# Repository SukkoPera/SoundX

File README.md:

# SoundX

SoundX is an Open Hardware sound card for the Commodore 16, 116 and Plus/4 home computers based on the Yamaha OPL/OPL-II chip.

## Summary
SoundX is basically an adaptation of the [C64 SFX Sound Expander](https://www.c64-wiki.com/wiki/Commodore_Sound_Expander) for the x264 series of Commodore computers.

While it didn't enjoy much success when it was released on the C64, since it was not that much superior to the built-in SID (if superior at all...), it would have certainly been much more successful if it had been targeted at the Commodore 16, 116 and Plus/4. In fact, it is basically the equivalent of an [AdLib](https://en.wikipedia.org/wiki/Ad_Lib,_Inc.#AdLib_Music_Synthesizer_Card_(1987)), an audio card for the PCs of the time, based on the YM3526 chip from Yamaha (also known as OPL), which is *exponentially* better than the TED as a sound chip, as it sports the following features (thanks [Wikipedia](https://en.wikipedia.org/wiki/Yamaha_OPL)):

- 9 channels of sound, each made of two oscillators or 6 channels with 5 percussion instruments

For every channel:
- Main frequency (10 bits)
- Octave (3 bits)
- Note on/off
- Synthesis mode (FM or just additive)
- Feedback (0–7, the modulator modulating itself)

For each one of the two oscillators:
- Frequency multiply (can be set to 1⁄2, 1 to 10, 12 or 15)
- Waveform (Sine)
- Volume (0–63, logarithmic)
- Attack, decay, sustain, release (4 bits each, logarithmic)
- Tremolo (on or off)
- Vibrato (on or off)
- Sustain (on or off)
- Envelope scaling per key (on or off)
- Volume scaling per key (0–3)

There are also a few parameters that can be set for the whole chip:
- Vibrato depth
- Tremolo depth
- Percussion mode (uses 3 channels to provide 5 percussion sounds)
- Composite sine mode (see Sinewave synthesis)

The board can even use the slightly more modern YM3812 (OPL-II): *among its newly-added features is the ability to pick between four waveforms for each individual oscillator. In addition to the original sine wave, three modified waveforms can be produced: half-sine waves (where the negative part of the sine is muted), absolute-sine waves (where the negative part is inverted), and pseudo-sawtooth waves (quarter sine waves upward only with silent sections in between)*.

### MIDI I/O
The original SFX Sound Expander could be bought [together with a piano-like keyboard](http://www.mssiah-forum.com/viewtopic.php?pid=4598#p4598) and some demo software. Such keyboard is not easy to find these days, so it was pointless to replicate the interface for it and I rather decided to build upon my experience with another project and add a real MIDI I/O interface. This means the C16/116/+4 will be able to receive data from a MIDI keyboard or to play it, through a **standard** DIN-5 MIDI interface.

## Versions
There are currently two versions of SoundX. Both have the same features and differ only in a few aspects, see below for more details.

## Design and Assembly Notes
This project makes sense because the YM3812 chip, its companion DAC (YM3014B) and an ACIA chip (for the MIDI part) can all be bought supercheap on AliExpress & similar sites, making this board very affordable to build for everyone. Let's say 15-20€? So get all this stuff second-hand and be happy :).

Remember to solder the JP5 jumper on the back of the board: I suggest the ON position unless you know what you are doing (check the schematics).

The audio output is automatically fed back into the computer through the EXT_AUDIO pin, so that you will hear it mixed with the sounds produced by the TED. There is also a 3.5" jack connector on the board, which allows bringing the sound output to external equipment. Note that when a jack is plugged in, the sound will no longer be redirected to the EXT_AUDIO pin.

Note that the OPL and MIDI circuits of the board are completely independent from each other, so the board can also be assembled partially if only one of the features is desired. The IBOM points out which feature every components belongs to.

### Version 1
Version 1 uses a standard ACIA 6551 chip for the MIDI interface. This is available from different manufacturers (MOS, Rockwell, and even [new from the Western Design Center](https://www.westerndesigncenter.com/wdc/w65c51s-chip.php)!) and requires a 3 MHz crystal to reach the MIDI baudrate.

The YM3812 requires an active oscillator either in DIP-8 or DIP-14 size.

There are some solder jumpers on the board:
- JP1: Close if your oscillator requires pin 1 to be grounded (uncommon).
- JP2: Close if you want the same signal sent to both channels of the jack connector.
- JP3/JP4: Close these to provide +5V on the normally-unused pins of the MIDI output connector: **this is non-standard and might actually damage the board or the connected device**, so keep these open unless you REALLY know what you are doing.
- JP5: The YM3812 can either go through a 15 kHz low-pass filter (ON) or not (BYPass): normally set to ON.

### Version 2
Version 2 switched the ACIA to a Motorola MC6850 chip that requires an active oscillator in DIP-8 size, running at either 500 kHz or 2 MHz. When using the 500 kHz oscillator, U5 and C12 are not required and can be skipped altogether.

In order to make space for the MC6850 oscillator, the YM3812 oscillator was also restricted to DIP-8 size.

Version 2 features additional jumpers:
- JP6: Same as JP1 for the MC6850 oscillator.
- JP7: Set in accordance with the oscillator frequency.
- JP8: Set to R/W and don't ask questions! If you want to know more, see [this](https://github.com/mist-devel/c64/issues/1).

## Programming
### OPL/OPL-II
Due to the impressive array of features, the OPL/OPL-II is not easy to program: the chip has 244 registers, so it would take a while to get acquainted with it and there is really not much documentation about how to program the SFX Sound Expander. This is one of the reasons why I decided to diverge a bit from the SFX Sound Expander on the programming side and rather followed the AdLib style: the board only uses two addresses for the audio part: $FDE4 and $FDE5. The former is for writing the number of the YM register to be modified while the latter is for the value. The former address can also be read and it will return the OPL status register, which is only useful for the detection of the board or if you want to make use of the OPL internal timers.

This means that you should be able to follow any AdLib programming tutorials around (like [this one](https://bochs.sourceforge.io/techspec/adlib_sb.txt)), as they should be 100% applicable to SoundX just as well (except for the different addresses, of course). The chip detection from that document also works!

> [!IMPORTANT]
> When programming the OPL chip, always keep in mind is that **you must wait at least 3.3 microseconds after you wrote the address, before you write the data, and then at least 23 microseconds before the next write**. This stands for AdLib sound cards as well, since it is an inherent limitation of the OPL chip. Nevertheless, [some clever programming](https://c64.xentax.com/index.php/15-testing-ym3812-register-write-timing) appears to be able to mitigate the issue.

### MIDI I/O - Version 1
The classic ACIA (6551) chip running the MIDI section uses addresses $FDE0/1/2/3 (I chose these addresses because they were already partly used by Solder's MIDI interface).

Configure the chip for:
- No Parity, No Echo, No TX Interrupt, /RTS Low (Unneeded), No RX Interrupt, /DTR Low (Unneeded) &rarr; $0b to Command Register
- 0 Stop Bits, 8 Data Bits, Internal Baud Rate Generator, 19200 bps (which will actually result in 31250 due to the use of the non-standard crystal) &rarr; $1f to Control Register

### MIDI I/O - Version 2
The MC6850 only has two register, which get mapped at $FDE0/1, which makes me think that this is exactly the same design used by Solder's interface. The software configuration is the same, regardless of what oscillator is installed: configure the chip for No interrupt, /RTS Low (Unneeded), 8 Data bits + 1 Stop bit, No Parity, Clock Divider = 16 (i.e.: $15)

> [!NOTE]
> Please always support both board versions in your projects. It is easy and you can find a driver that does so on the [Wiki](https://github.com/SukkoPera/SoundX/wiki).

### Examples
If you want some code to start from, you can have a look at the [Tech Demo that Master Csabo from the Plus/4 World Forum quickly hacked together](https://plus4world.powweb.com/software/YM3812_Tech_Demo): it does OPL detection and then plays a few songs from the original [AdLib Card Demo](https://vgmrips.net/packs/pack/adlib-music-synthesizer-card-demo-songs-ibm-pc-xt-at). It comes with full source code, so it will definitely be helpful!

Csabo has also made a [Simple MIDI Decoder](https://plus4world.powweb.com/software/Simple_MIDI_Decoder) utility that listens for NoteOn and NoteOff messages coming in through the MIDI port and plays the corresponding notes through the TED. Again, it comes with full source code and thus it should help you have a jump start.

## Next Steps
Of course, to make complete sense, this project needs support from the actual programmers! So people, please make games for the board! Or programs, demos, whatever! I think a nice first step would be to port [the original SFX Sounds Expander software](https://csdb.dk/release/?id=155181): I can't say for sure, but I'm guessing this shouldn't be too much of an effort, plus I can help with the tech details and can explain how to make the MIDI decoder, just ask! :)

## Releases
If you want to get this board produced, you are recommended to get [the latest release](https://github.com/SukkoPera/SoundX/releases) rather than the current git version, as the latter might be under development and is not guaranteed to be working.

Every release is accompanied by its Bill Of Materials (BOM) file and any relevant notes about it, which you are recommended to read carefully.

## License
The SoundX documentation, including the design itself, is copyright &copy; SukkoPera 2023-2025 and is licensed under the [Creative Commons Attribution-NonCommercial-ShareAlike 4.0 International License](https://creativecommons.org/licenses/by-nc-sa/4.0/).

This documentation is distributed *as is* and WITHOUT ANY EXPRESS OR IMPLIED WARRANTIES whatsoever with respect to its functionality, operability or use, including, without limitation, any implied warranties OF MERCHANTABILITY, SATISFACTORY QUALITY, FITNESS FOR A PARTICULAR PURPOSE or infringement. We expressly disclaim any liability whatsoever for any direct, indirect, consequential, incidental or special damages, including, without limitation, lost revenues, lost profits, losses resulting from business interruption or loss of data, regardless of the form of action or legal theory under which the liability may be asserted, even if advised of the possibility or likelihood of such damages.

## Support the Project
If you want to get some boards manufactured, you can get them from PCBWay through this link:

You get my gratitude and cheap, professionally-made and good quality PCBs, I get some credit that will help with this and [other projects](https://www.pcbway.com/project/member/?bmbno=72D33927-5EF6-42). You won't even have to worry about the various PCB options, it's all pre-configured for you!

Also, if you still have to register, [you can use this link](https://www.pcbway.com/setinvite.aspx?inviteid=41100) to get some bonus initial credit (and yield me some more).

You can also buy me a coffee if you want, all the money collected this way will actually go to charity:

## Thanks
* Master Csabo and Chizman (unbeknownst) for their help with the testing software.
* kinmami for his usual precious hints about the hardware design.
* Iconian Fonts (Daniel Zadorozny) for the [Universal Jack Font](https://www.fontspace.com/universal-jack-font-f101650) used for the logo.

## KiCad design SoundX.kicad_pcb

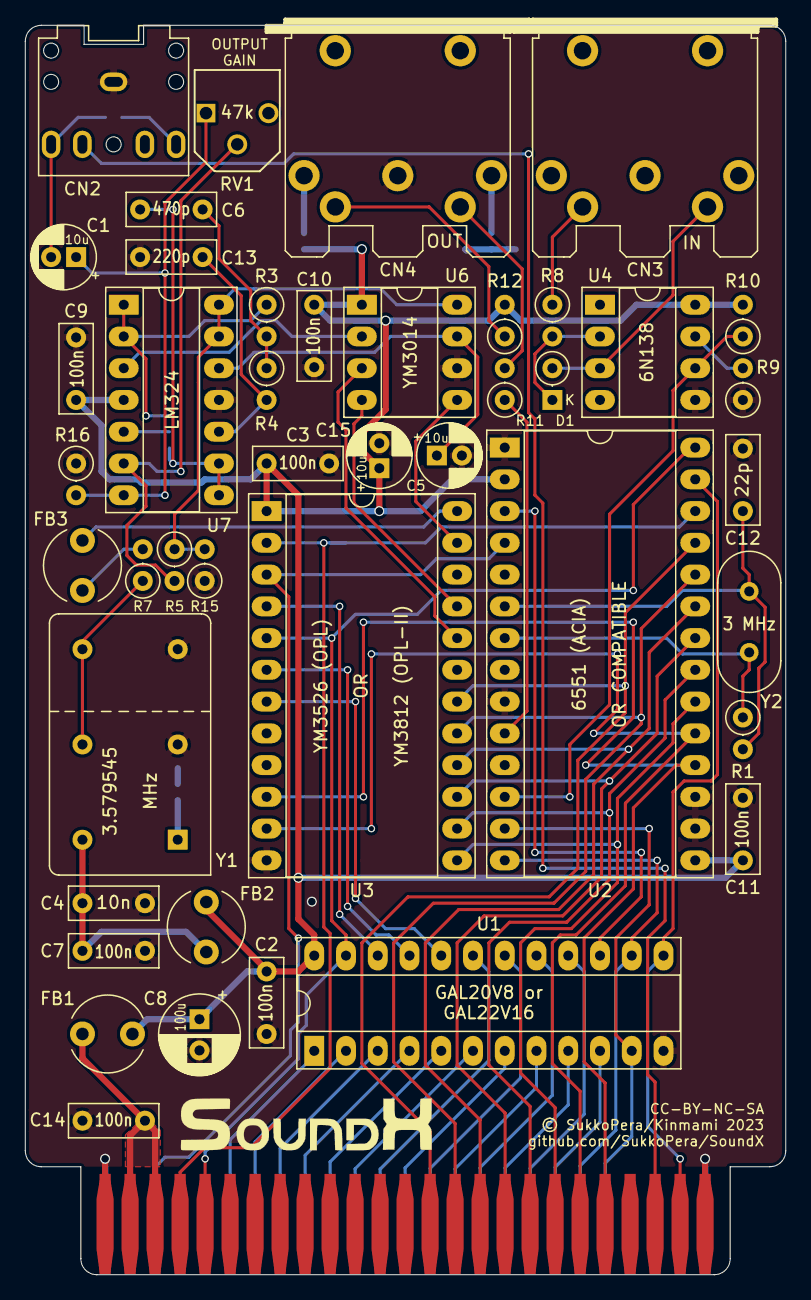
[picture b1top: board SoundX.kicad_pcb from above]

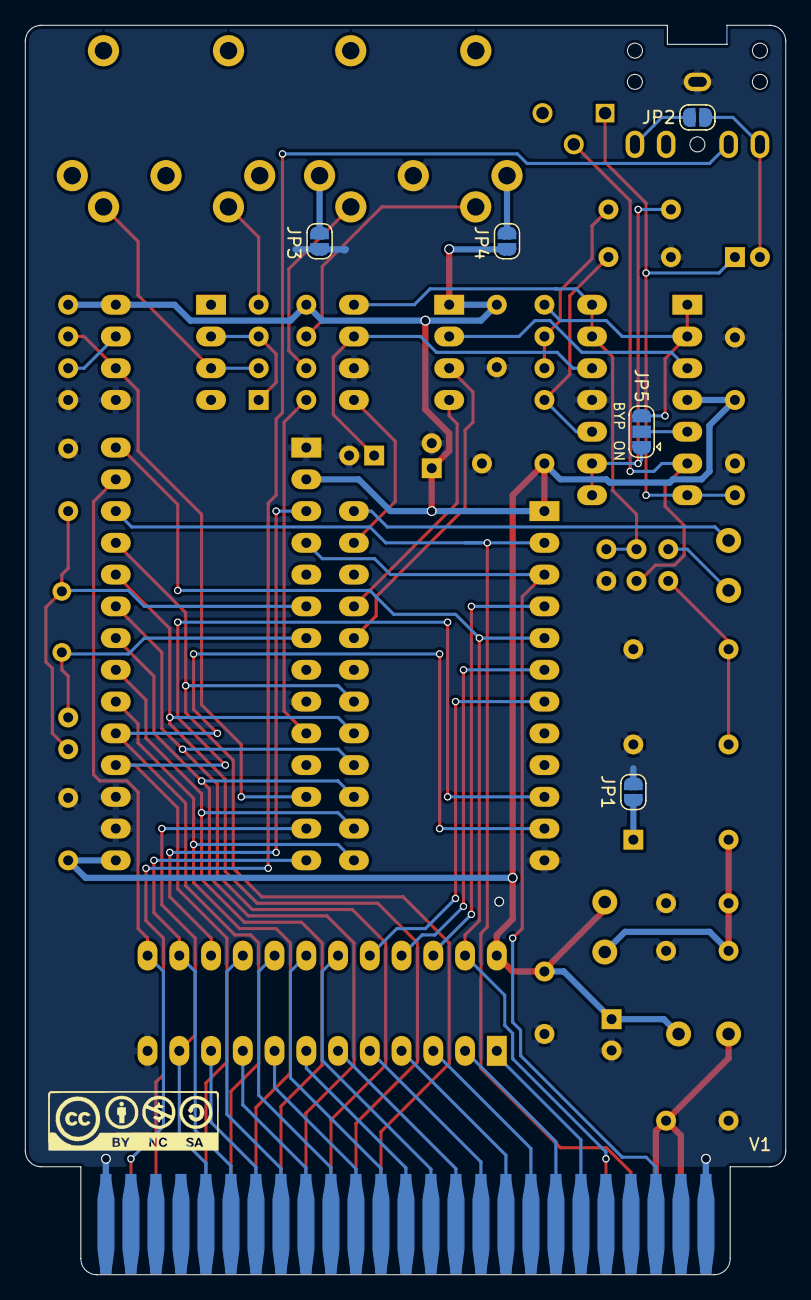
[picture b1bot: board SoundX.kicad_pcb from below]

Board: 2 copper layers, 60.8 x 99.9 mm, 51 parts (6 on the bottom side), 68 nets.

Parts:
C1, C5, C15: 10u; CP_Radial_D5.0mm_P2.00mm
C2, C3, C7, C9, C10, C11, C14: 100n; C_Disc_D7.0mm_W2.5mm_P5.00mm
C4: 10n; C_Disc_D7.0mm_W2.5mm_P5.00mm
C6: 470p; C_Disc_D7.0mm_W2.5mm_P5.00mm
C8: 100u; CP_Radial_D6.3mm_P2.50mm
C12: 22p; C_Disc_D7.0mm_W2.5mm_P5.00mm
C13: 220p; C_Disc_D7.0mm_W2.5mm_P5.00mm
CN1: EDGE_CONN; C16_Cart_Conn
CN2: RAW_AUDIO_OUT; AudioJack_SJ1-3525N
CN3: CONN_MIDI_IN; DIN5
CN4: CONN_MIDI_OUT; DIN5
D1: 1n4148; D_DO-35_SOD27_P2.54mm_Vertical_KathodeUp
FB1, FB2, FB3: FERRITE; L_Radial_D6.0mm_P4.00mm
JP1: JMP_OSC_PIN1; SolderJumper-2_P1.3mm_Open_RoundedPad1.0x1.5mm
JP2: JMP_STEREO; SolderJumper-2_P1.3mm_Open_RoundedPad1.0x1.5mm
JP3: JMP_POM_GND; SolderJumper-2_P1.3mm_Open_RoundedPad1.0x1.5mm
JP4: JMP_POM_VCC; SolderJumper-2_P1.3mm_Open_RoundedPad1.0x1.5mm
JP5: JMP_FILTER_BYPASS; SolderJumper-3_P1.3mm_Open_RoundedPad1.0x1.5mm
R1: 1M; R_Axial_DIN0207_L6.3mm_D2.5mm_P2.54mm_Vertical
R3, R4: 33k; R_Axial_DIN0207_L6.3mm_D2.5mm_P2.54mm_Vertical
R5: 15k; R_Axial_DIN0207_L6.3mm_D2.5mm_P2.54mm_Vertical
R7: 47; R_Axial_DIN0207_L6.3mm_D2.5mm_P2.54mm_Vertical
R8, R10, R11, R12: 220; R_Axial_DIN0207_L6.3mm_D2.5mm_P2.54mm_Vertical
R9, R15: 4.7k; R_Axial_DIN0207_L6.3mm_D2.5mm_P2.54mm_Vertical
R16: 10k; R_Axial_DIN0207_L6.3mm_D2.5mm_P2.54mm_Vertical
RV1: 47k; Pot_Bourns_3306P
U1: GAL20V8; DIP-24_W7.62mm_Socket_LongPads
U2: MOS_6551_ACIA; DIP-28_W15.24mm_Socket_LongPads
U3: YM3526; DIP-24_W15.24mm_Socket_LongPads
U4: 6N138; DIP-8_W7.62mm_Socket_LongPads
U6: YM3014; DIP-8_W7.62mm_Socket_LongPads
U7: LM324; DIP-14_W7.62mm_Socket_LongPads
V0: CC-BY-NC-SA; cc_by_nc_sa
V1: LOGO; logo
Y1: 3.579545 MHz; Oscillator_DIP-8+14
Y2: 3M; Crystal_HC49-U_Vertical

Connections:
+5V: C2.1, C3.1, C8.1, C9.1, C10.1, C11.1, C15.1, FB1.2, FB2.2, JP4.1, R10.2, R12.2, U1.24, U2.2, U2.15, U3.1, U4.8, U6.1, U7.4
/a0: CN1.Y, U1.11, U2.13
/a1: CN1.X, U1.14, U2.14
/a2: CN1.W, U1.10
/a3: CN1.V, U1.16
/a4: CN1.U, U1.9
/a5: CN1.T, U1.17
/a6: CN1.S, U1.8
/a7: CN1.R, U1.18
/a8: CN1.P, U1.7
/a9: CN1.N, U1.19
/a10: CN1.M, U1.6
/a11: CN1.L, U1.5
/a12: CN1.K, U1.4
/a13: CN1.J, U1.3
/a14: CN1.H, U1.2
/a15: CN1.F, U1.1
/amp_in: JP5.2, U7.5
/clock: FB3.1, U3.24
/d0: CN1.21, U2.18, U3.10
/d1: CN1.20, U2.19, U3.11
/d2: CN1.19, U2.20, U3.13
/d3: CN1.18, U2.21, U3.14
/d4: CN1.17, U2.22, U3.15
/d5: CN1.16, U2.23, U3.16
/d6: CN1.15, U2.24, U3.17
/d7: CN1.14, U2.25, U3.18
/dac_clk: U3.20, U6.3
/dac_sync: U3.23, U6.5
/ext_audio: CN1.23, CN2.TN
/flt_in: JP5.3, R3.1, U7.1, U7.2
/flt_out: C6.2, JP5.1, U7.8, U7.9
/phi2: CN1.24, U1.13, U2.27
/q+: C12.1, R1.2, U2.6, Y2.2
/q-: R1.1, U2.7, Y2.1
/r_~w: CN1.5, U1.23, U2.28, U3.5
/rxd_ttl: R10.1, U2.12, U4.6
/ser_audio: U3.21, U6.4
/txd_ttl: R11.1, U2.10
/ym_a0: U1.22, U3.4
/~irq: CN1.4, U2.26, U3.2
/~midi_cs: U1.15, U2.3
/~reset: CN1.C, U2.4, U3.3
/~ym_cs: U1.20, U3.7
/~ym_rd: U1.21, U3.6
GND: C2.2, C3.2, C4.2, C5.2, C7.2, C8.2, C9.2, C10.2, C11.2, C12.2, C13.2, C14.2, C15.2, CN1.1, CN1.25, CN1.A, CN1.CC, CN2.S, CN4.2, JP1.2, JP3.1, R9.1, R15.1, R16.1, U1.12, U2.1, U2.9, U2.16, U2.17, U3.12, U4.5, U6.6, U7.11, Y1.7
unnamed: C1.1, R16.2, RV1.1, U7.7
unnamed: C1.2, CN2.T, JP2.1
unnamed: C4.1, C7.1, FB2.1, Y1.14
unnamed: C5.1, U6.7, U7.12
unnamed: C6.1, R3.2, R4.1
unnamed: C13.1, R4.2, U7.10
unnamed: C14.1, CN1.2, CN1.3, FB1.1
unnamed: CN2.R, JP2.2
unnamed: CN3.4, R8.1
unnamed: CN3.5, D1.2, U4.3
unnamed: CN4.1, JP4.2
unnamed: CN4.3, JP3.2
unnamed: CN4.4, R12.1
unnamed: CN4.5, R11.2
unnamed: D1.1, R8.2, U4.2
unnamed: FB3.2, R7.2
unnamed: JP1.1, Y1.1
unnamed: R5.2, RV1.2, U7.6
unnamed: R7.1, Y1.8
unnamed: R9.2, U4.7
unnamed: R5.1, R15.2, U6.8, U7.13, U7.14
unnamed: U6.2, U7.3

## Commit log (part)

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2023-08-16 Rough routing complete, even not that rough
2023-08-17 First round of improvements by @kinmami
2023-08-17 Add logo
2023-08-17 Add filter bypass jumper
2023-08-17 Tidy up silkscreen
2023-08-17 Final touches
2023-08-19 Second round of improvements by @kinmami
2023-08-19 Add output gain pot
2023-08-19 Add detail of components belonging to OPL or MIDI circuit
2023-08-19 Move C13 up
2023-08-20 Rewrite equations for AdLib-style (2 registers only for YM)
2023-08-20 Better equations for MIDI
2023-12-21 Add README
2023-12-21 Change OPL addresses to $FDE4/5
2023-12-22 Move GAL files to where they belong
2023-12-23 Add some P/Ns
2023-12-23 Update board link
2023-12-23 Add renders
2024-08-13 Version with MC6850 should be ready
2024-08-13 Switch to 2 oscillators (and KiCad 8)
2024-08-13 Final touches for V2
2024-08-13 Update edge connector
2024-08-13 Fixes after rebasing (???)
2024-08-13 Readd some P/Ns and add 5mm-pitch footprint for DIN-5 connector
2024-08-14 Add clock divider for ACIA
2024-08-16 Add RW/A1 jumper This is inspired by some C64 interfaces
2024-08-16 Add docs for some C64 interfaces
2025-01-28 44-pin version of V2
2025-01-29 Better edge connector
2025-01-29 Final touches for v2_44
2026-02-13 Update donation link and image in README
    Updated the 'Buy Me a Coffee' link and image.
2026-03-04 Update renders
2026-03-04 Fix PCBWay link

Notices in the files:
SoundX.kicad_pcb:
Licensed under CC BY-NC-SA 4.0
© SukkoPera/Kinmami 2023
